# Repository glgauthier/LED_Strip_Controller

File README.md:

#LED Strip Controller

A project for controlling cheap 5050 LED strips better than their factory 
made controllers. 

#Version 1 (Completed):
-Support for the features found in the factory controller as well as
audio response

-Uses button input rather than IR remote

-Based on ATMEGA328P with Arduino bootloader

#Version 2 (In the works):
-Same features as previous version as well as an added IR receiver so
that it can work with any remote

-Much cleaner code, schematic, and board design

-Based on ATTINY85; cheaper and just as useful!

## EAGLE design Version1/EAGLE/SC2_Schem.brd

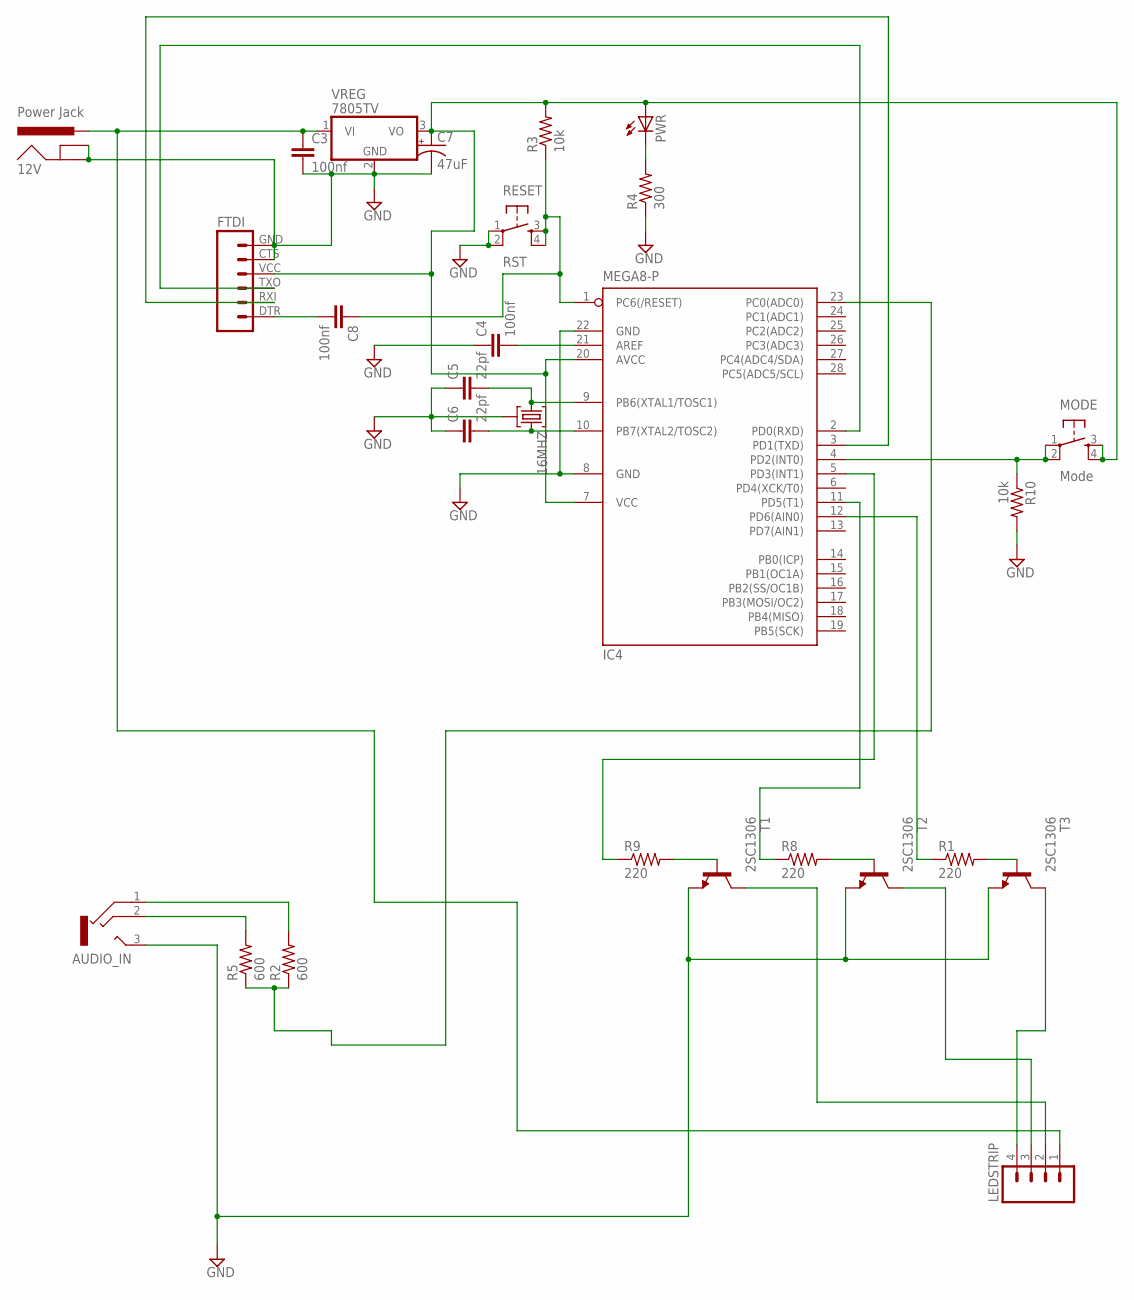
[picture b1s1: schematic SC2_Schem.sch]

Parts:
12V: Power Jack; POWER_JACK_PTH
16MHZ: 10G7A-12.5KHZ; HC49U
AUDIO_IN: 1503_04
C3, C4, C8: 100nf; CAP-PTH-5MM
C5, C6: 22pf; CAP-PTH-5MM
C7: 47uF; CPOL-RADIAL-100UF-25V
FTDI: FTDI_BASICPTH; FTDI_BASIC
IC4: MEGA8-P; DIL28-3
LEDSTRIP: M041X04_NO_SILK; 1X04_NO_SILK
MODE: Mode; TACTILE-PTH
PWR: LED5MM
R1, R8, R9: 220; AXIAL-0.3
R2, R5: 600; AXIAL-0.3
R3: 10k; AXIAL-0.3EZ
R4: 300; AXIAL-0.3EZ
R10: 10k; AXIAL-0.3
RESET: RST; TACTILE-PTH
T1, T2, T3: 2SC1306; TO220BV
VREG: 7805TV; TO220V

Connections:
GND: 12V.GND, 12V.GNDBREAK, 16MHZ.2, AUDIO_IN.3 (2), C3.2, C4.1, C5.1, C6.1, C7.2 (-), FTDI.CTS (5), FTDI.GND (6), IC4.8 (GND), IC4.22 (GND), R4.P$1 (1), R10.P$2 (2), RESET.1, RESET.2, T1.3 (E), T2.3 (E), T3.3 (E), VREG.2 (GND)
unnamed: R9.P$2 (2), T1.1 (B)
unnamed: IC4.23 (PC0(ADC0)), R2.P$1 (1), R5.P$1 (1)
unnamed: C4.2, IC4.21 (AREF)
unnamed: PWR.K (C), R4.P$2 (2)
unnamed: R8.P$2 (2), T2.1 (B)
unnamed: AUDIO_IN.1, R2.P$2 (2)
unnamed: R1.P$2 (2), T3.1 (B)
unnamed: IC4.5 (PD3(INT1)), R9.P$1 (1)
unnamed: IC4.11 (PD5(T1)), R8.P$1 (1)
unnamed: 16MHZ.1, C5.2, IC4.9 (PB6(XTAL1/TOSC1))
unnamed: 16MHZ.3, C6.2, IC4.10 (PB7(XTAL2/TOSC2))
unnamed: AUDIO_IN.2 (3), R5.P$2 (2)
unnamed: C8.1, IC4.1 (PC6(/RESET)), R3.P$1 (1), RESET.3, RESET.4
unnamed: FTDI.TXO (3), IC4.2 (PD0(RXD))
unnamed: FTDI.RXI (2), IC4.3 (PD1(TXD))
unnamed: C8.2, FTDI.DTR (1)
unnamed: IC4.12 (PD6(AIN0)), R1.P$1 (1)
unnamed: IC4.4 (PD2(INT0)), MODE.1, MODE.2, R10.P$1 (1)
unnamed: LEDSTRIP.2, T1.2 (C)
unnamed: LEDSTRIP.3, T2.2 (C)
unnamed: LEDSTRIP.4, T3.2 (C)
unnamed: C7.1 (+), FTDI.VCC (4), IC4.7 (VCC), IC4.20 (AVCC), MODE.3, MODE.4, PWR.A, R3.P$2 (2), VREG.3 (VO)
V+: 12V.PWR, C3.1, LEDSTRIP.1, VREG.1 (VI)

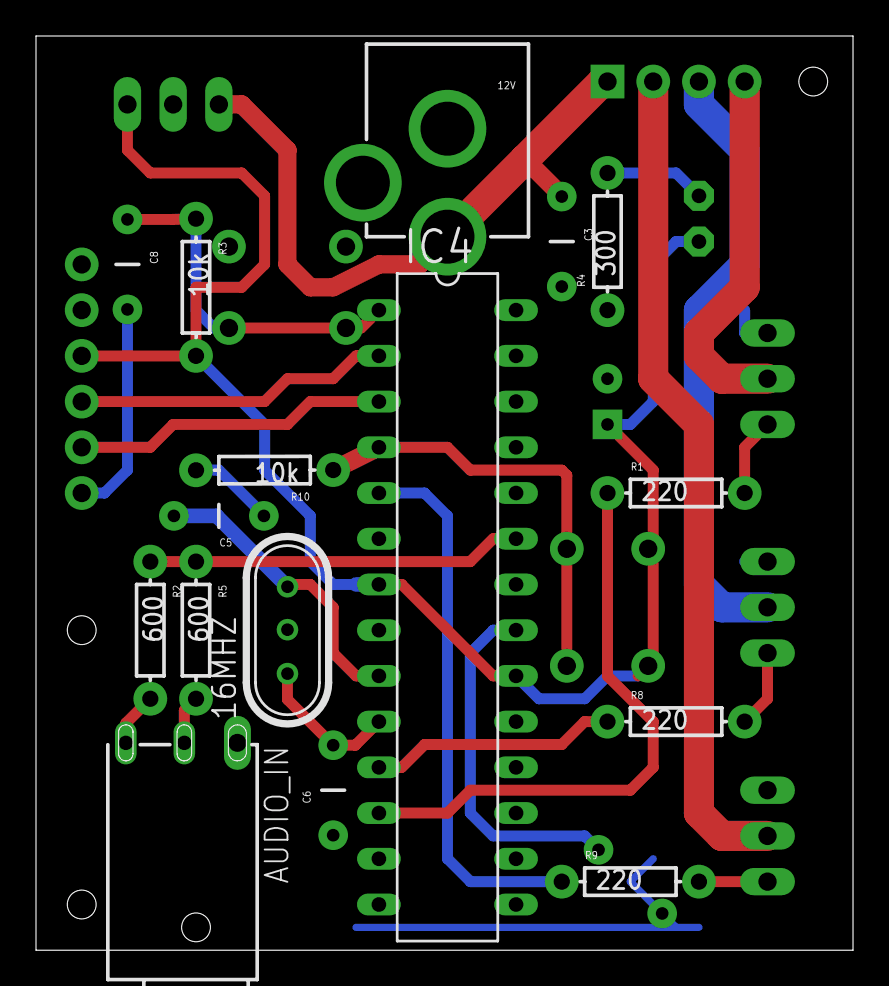
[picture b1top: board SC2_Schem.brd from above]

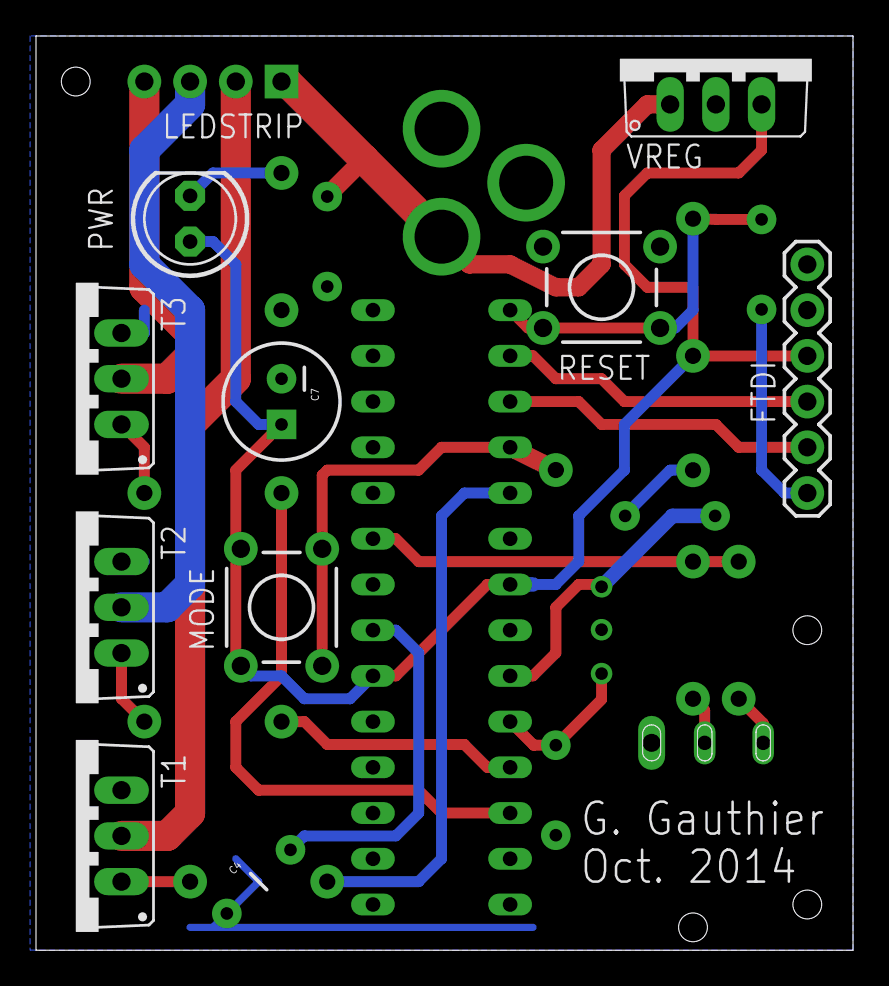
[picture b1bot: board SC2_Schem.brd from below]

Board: 2 copper layers, 45.4 x 50.8 mm, 27 parts (11 on the bottom side), 24 nets.

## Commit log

2015-06-27 Initial Commit
    added readme, code and board designs for R1

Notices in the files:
parts and their libraries:
SparkFun-Connectors: Licensing: Creative Commons ShareAlike 4.0 International - https://creativecommons.org/licenses/by-sa/4.0
